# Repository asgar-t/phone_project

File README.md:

# 📱 Phone Project

A custom embedded hardware project built around an STM32 microcontroller and Quectel EC25 modem.  
The goal is to design, assemble, and program a complete phone system from the ground up — starting with hardware validation and moving toward a full integrated board.

---

## 🚀 Project Overview

**Step 1 — Hardware Verification (current step)** 
- Bring-up of the main board and peripheral circuits  
- Validate power rails, charging system, and USB interface  
- Test modem communication (EC25) and antenna performance  
- Ensure STM32 programming and serial communication are functional  

**Step 2 — Full System Integration**
- Run the STM32 firmware with modem control and battery management  
- Implement power sequencing and graceful shutdown logic  
- Test full end-to-end operation (voice/data + MCU control)  
- Optimize PCB layout and firmware reliability for production

---

## 🧠 Skills Demonstrated
- **PCB Design:** High-speed routing, impedance control, power delivery, and signal integrity  
- **Embedded Programming:** STM32 firmware (C), peripheral interfacing (UART, USB, GPIO, ADC)  
- **Power Systems:** Battery charging, voltage regulation, and load-sharing design  
- **System Integration:** Combining modem, MCU, and power management into a cohesive embedded system  

---

## ⚙️ Technologies & Components
- **MCU:** STM32 L4 Series
- **Modem:** Quectel EC25-AF  
- **Power:** USB-C input, Li-ion battery, charger IC 
- **Communication:** USB, UART, CAN 
- **Tools:** KiCad, STM32CubeIDE

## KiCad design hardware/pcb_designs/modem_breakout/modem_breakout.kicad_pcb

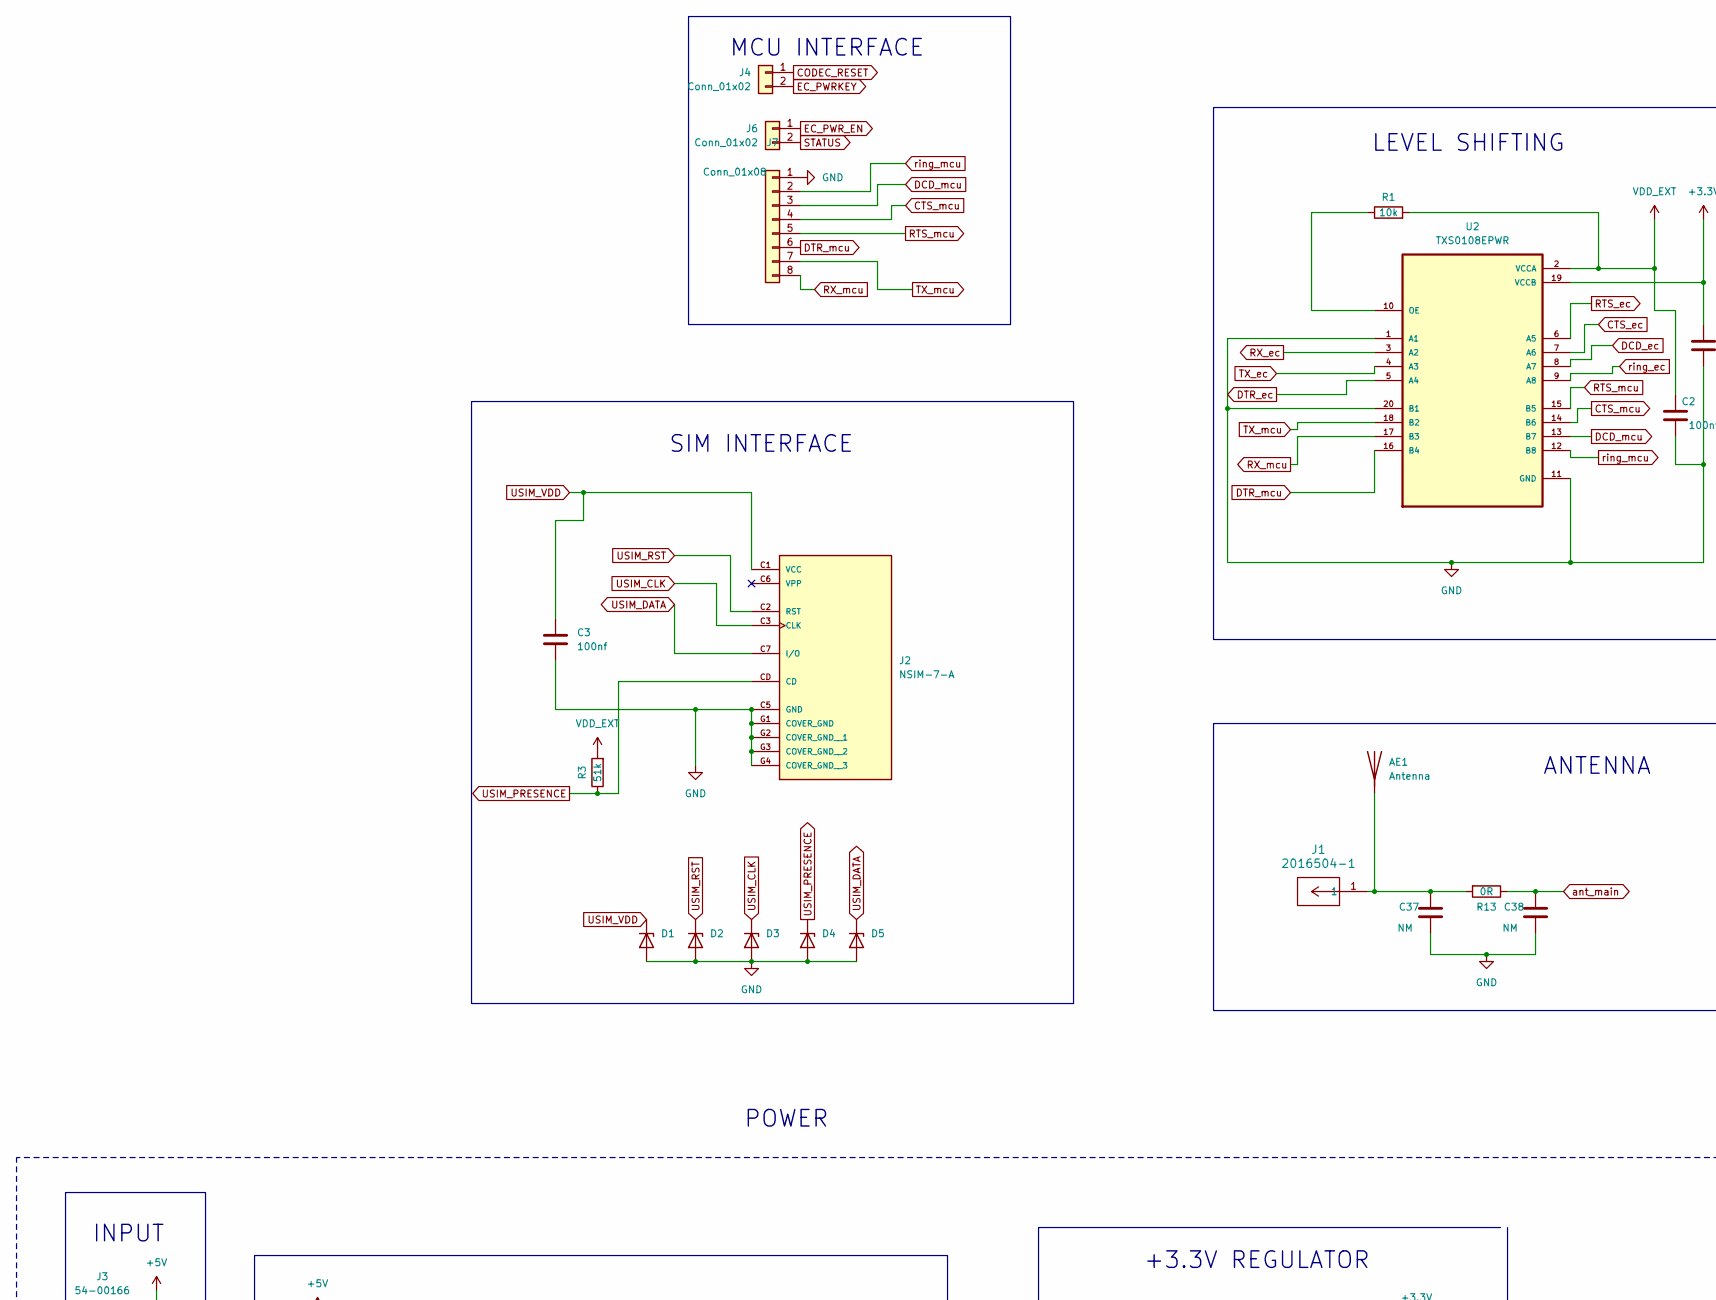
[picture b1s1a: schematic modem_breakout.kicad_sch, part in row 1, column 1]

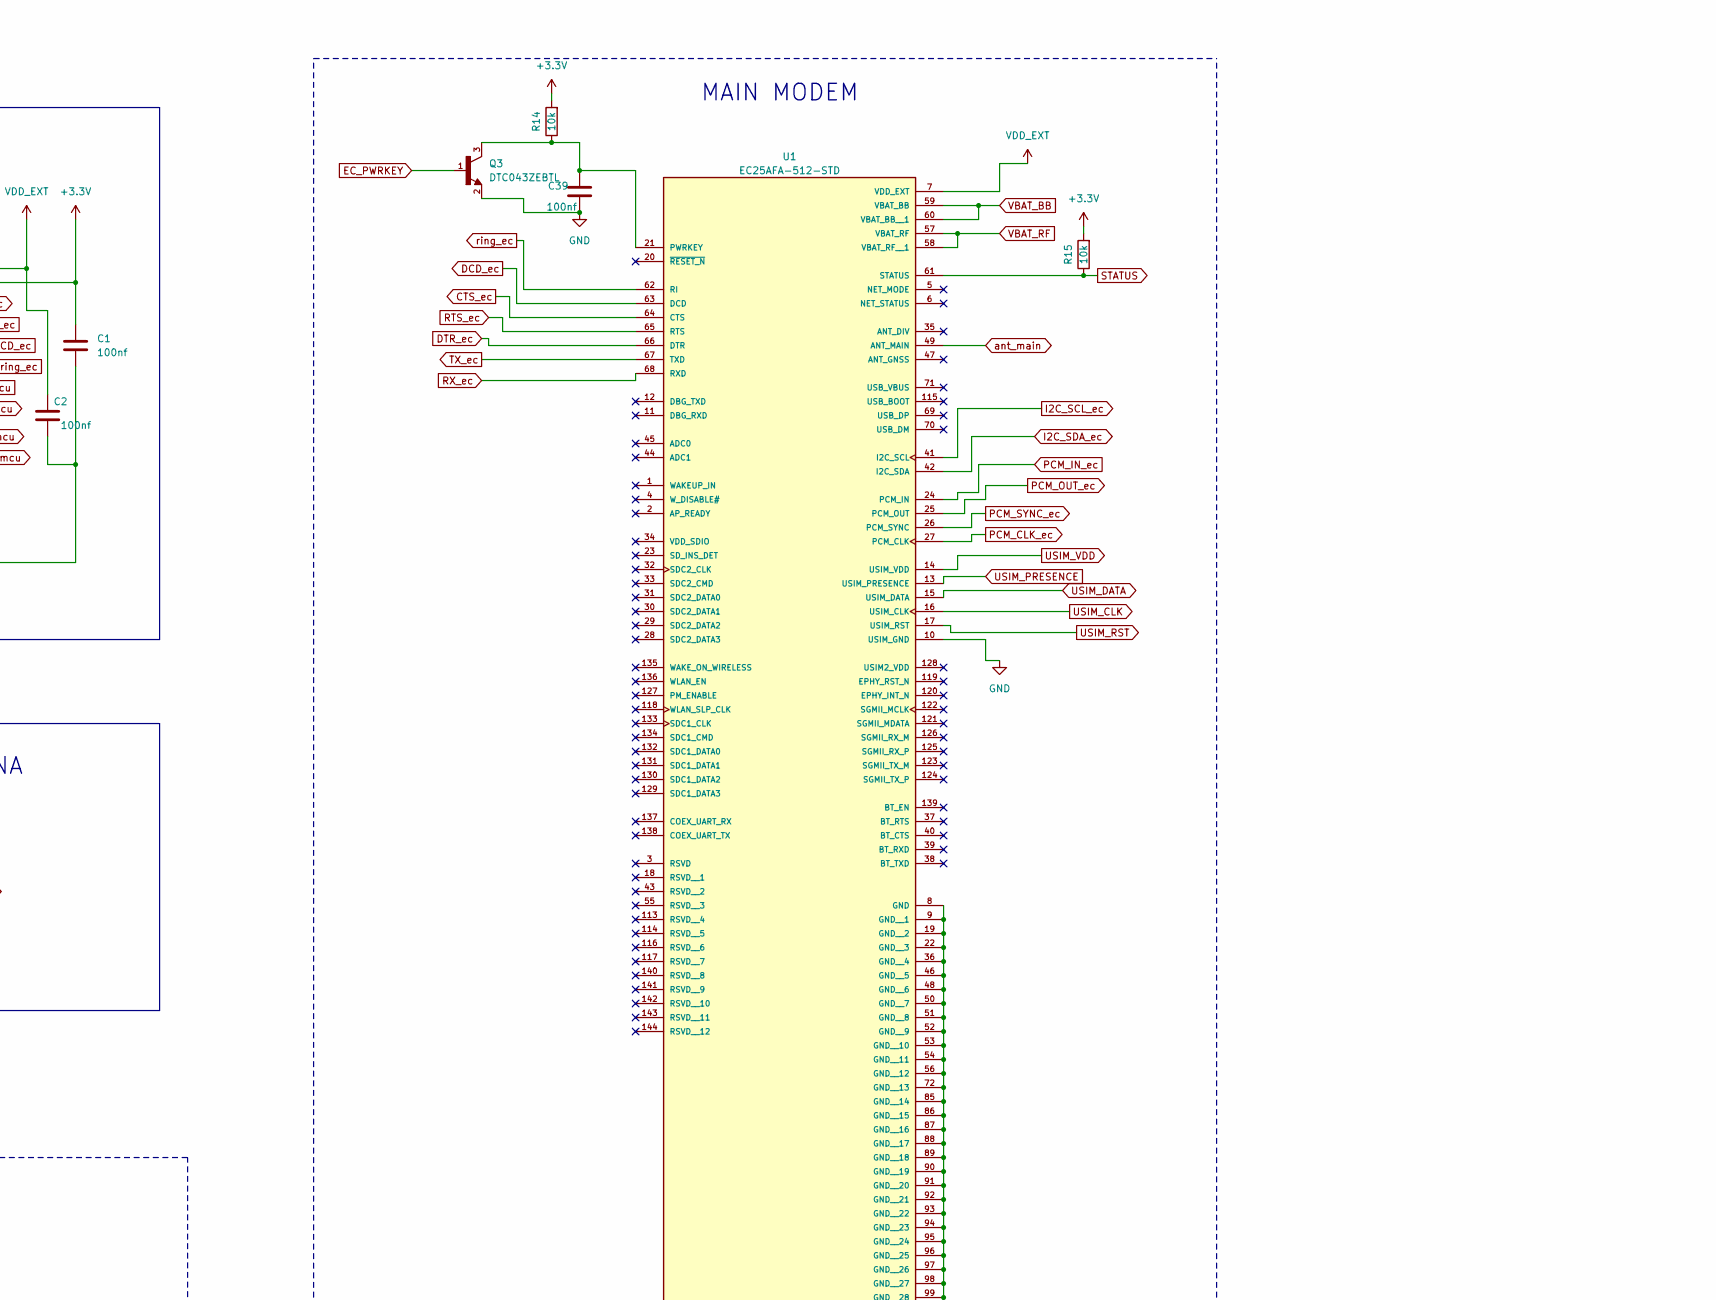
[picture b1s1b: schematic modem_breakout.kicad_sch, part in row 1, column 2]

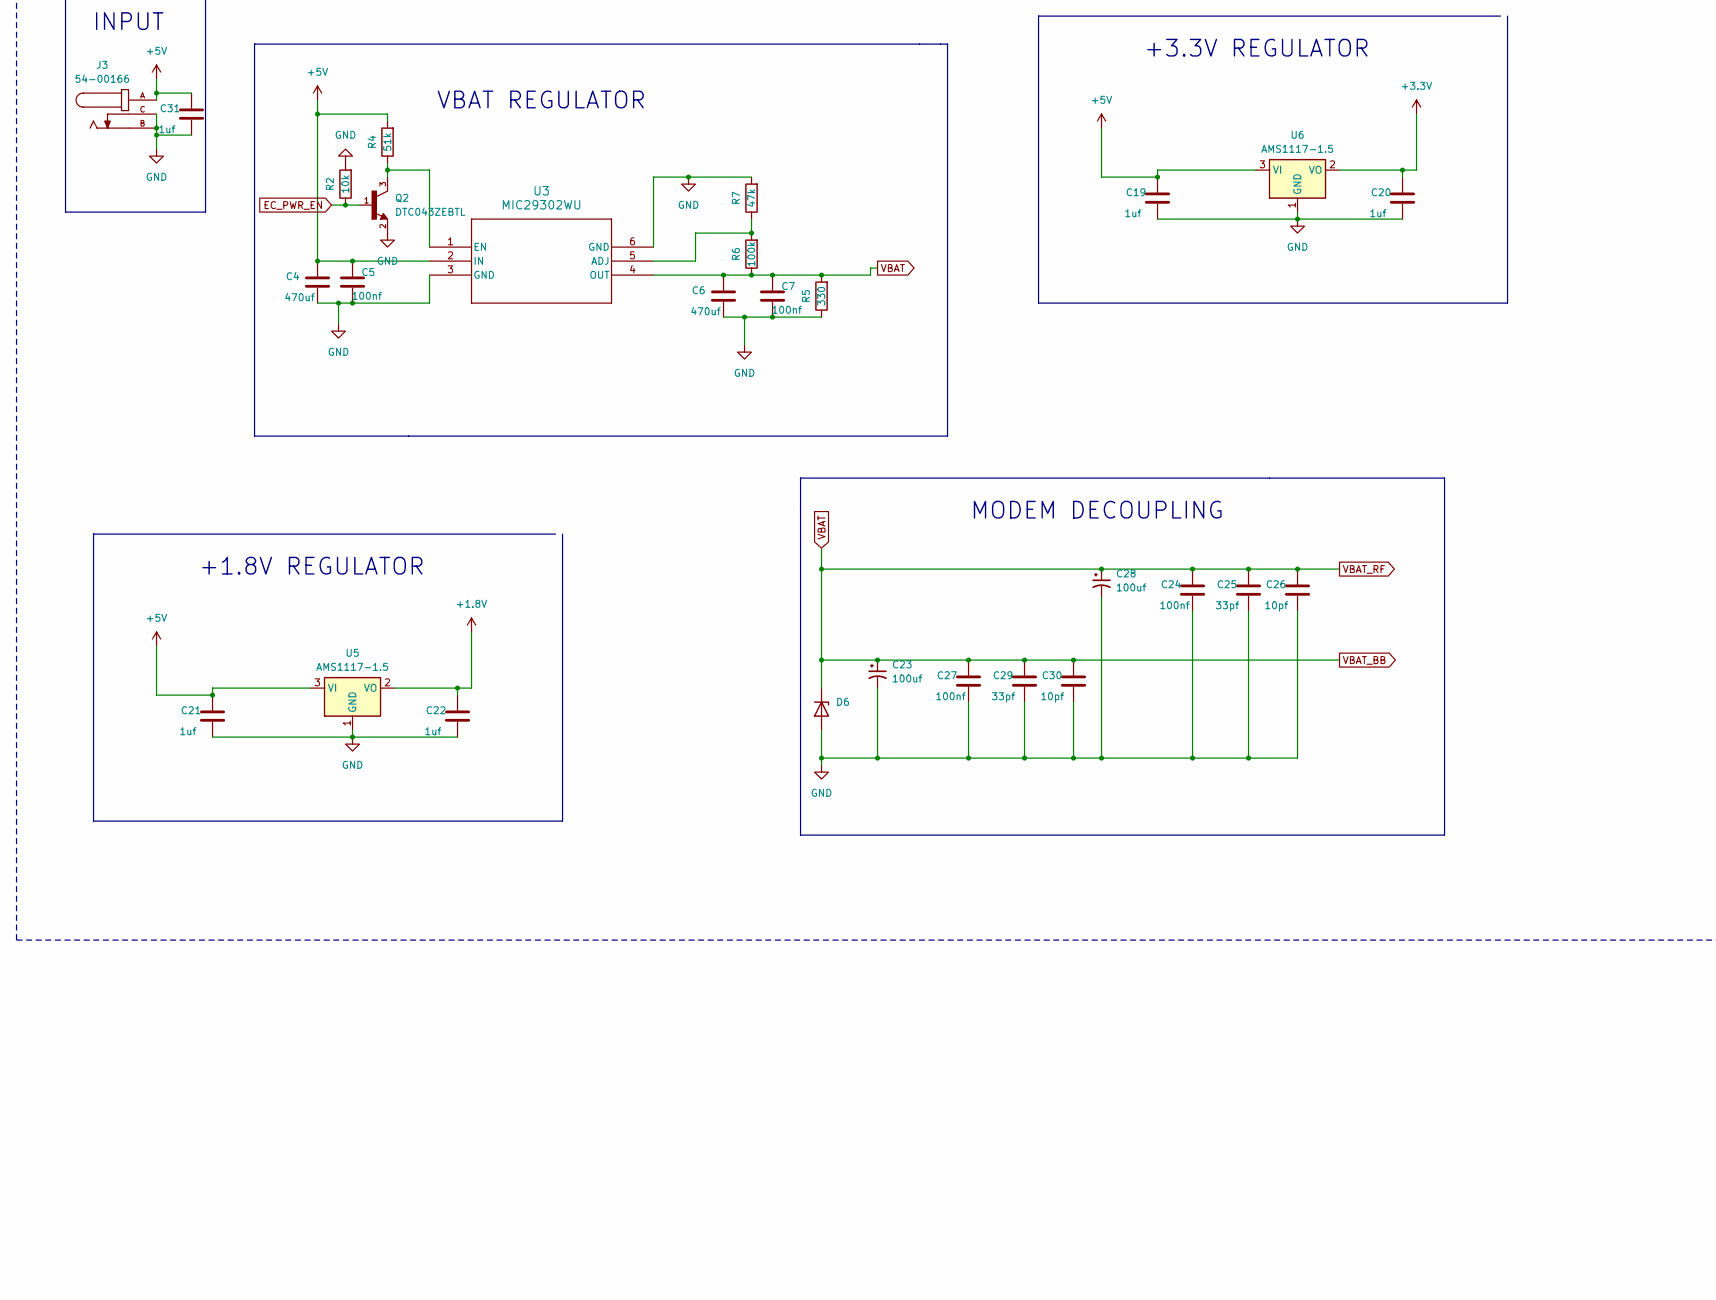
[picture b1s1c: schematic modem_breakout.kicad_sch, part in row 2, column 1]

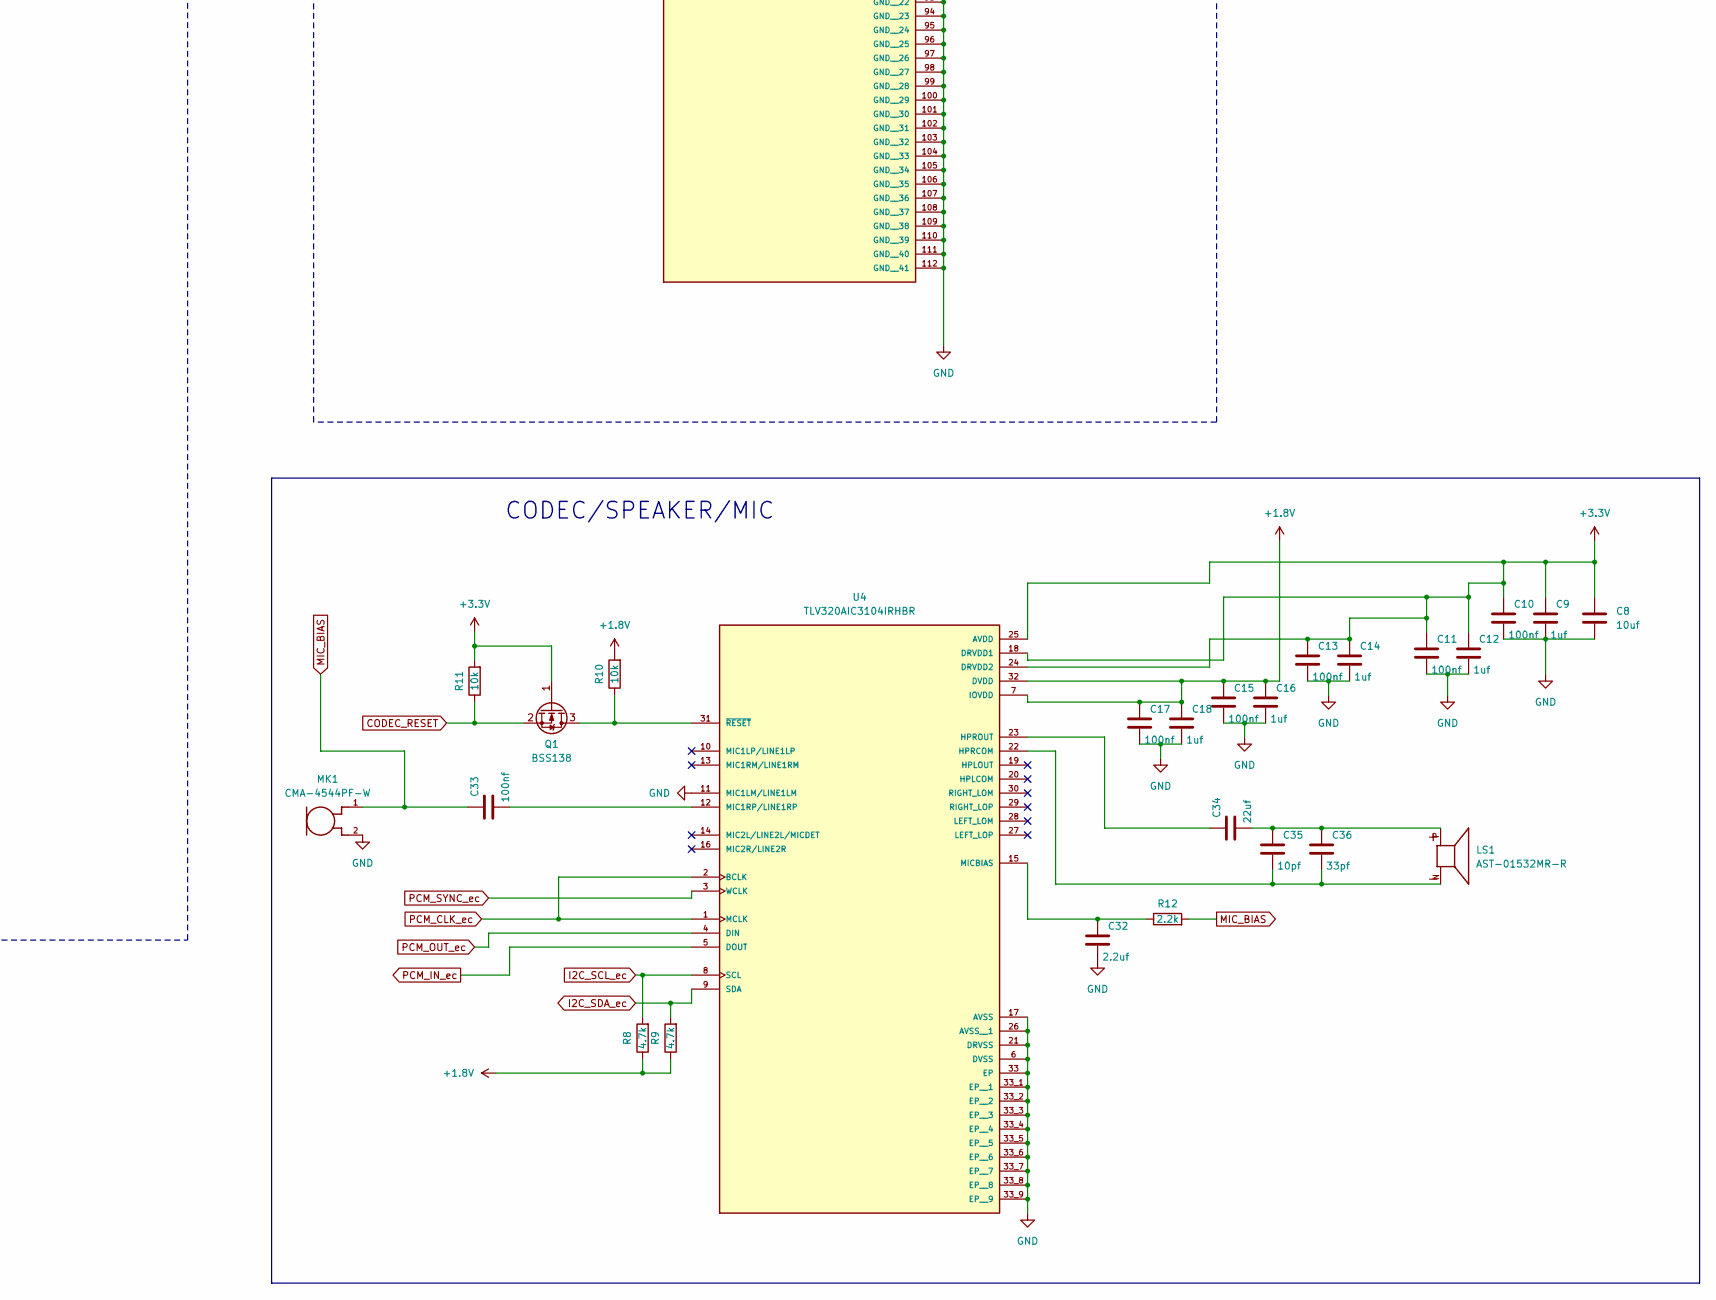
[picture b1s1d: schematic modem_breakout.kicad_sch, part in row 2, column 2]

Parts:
AE1: Antenna
C1, C2, C3, C5, C7, C24, C27, C33, C39: 100nf; C_0805_2012Metric_Pad1.18x1.45mm_HandSolder
C4, C6: 470uf; C_0805_2012Metric_Pad1.18x1.45mm_HandSolder
C8: 10uf; C_0402_1005Metric_Pad0.74x0.62mm_HandSolder
C9, C12, C14, C16, C18: 1uf; C_0402_1005Metric_Pad0.74x0.62mm_HandSolder
C10, C11, C13, C15, C17: 100nf; C_0402_1005Metric_Pad0.74x0.62mm_HandSolder
C19, C20, C21, C22, C31: 1uf; C_0805_2012Metric_Pad1.18x1.45mm_HandSolder
C23, C28: 100uf; C_0805_2012Metric_Pad1.18x1.45mm_HandSolder
C25, C29, C36: 33pf; C_0805_2012Metric_Pad1.18x1.45mm_HandSolder
C26, C30, C35: 10pf; C_0805_2012Metric_Pad1.18x1.45mm_HandSolder
C32: 2.2uf; C_0805_2012Metric_Pad1.18x1.45mm_HandSolder
C34: 22uf; C_0805_2012Metric_Pad1.18x1.45mm_HandSolder
C37, C38: NM; C_0805_2012Metric_Pad1.18x1.45mm_HandSolder
D1, D2, D3, D4, D5, D6: PTVS12VZ1USK; Nexperia_DSN1608-2_1.6x0.8mm
J1: 2016504-1; CONN1_2016504-1_TEC
J2: NSIM-7-A; new_sim; PARTREV 1.0
J3: 54-00166; barrel jack; PARTREV A
J4, J6: Conn_01x02; PinHeader_1x02_P2.54mm_Vertical
J7: Conn_01x08; PinHeader_1x08_P2.54mm_Vertical
LS1: AST-01532MR-R; SPKR_AST-01532MR-R; PARTREV A
MK1: CMA-4544PF-W; MIC_CMA-4544PF-W
Q1: BSS138; SOT-23
Q2, Q3: DTC043ZEBTL; SOTFL50P160X85-3N; PARTREV 002
R1, R2, R14, R15: 10k; C_0805_2012Metric_Pad1.18x1.45mm_HandSolder
R3, R4: 51k; C_0805_2012Metric_Pad1.18x1.45mm_HandSolder
R5: 330; C_0805_2012Metric_Pad1.18x1.45mm_HandSolder
R6: 100k; C_0805_2012Metric_Pad1.18x1.45mm_HandSolder
R7: 47k; C_0805_2012Metric_Pad1.18x1.45mm_HandSolder
R8, R9: 4.7k; C_0805_2012Metric_Pad1.18x1.45mm_HandSolder
R10, R11: 10k; C_0402_1005Metric_Pad0.74x0.62mm_HandSolder
R12: 2.2k; C_0805_2012Metric_Pad1.18x1.45mm_HandSolder
R13: 0R; C_0805_2012Metric_Pad1.18x1.45mm_HandSolder
U1: EC25AFA-512-STD; modem
U2: TXS0108EPWR; uart_translator
U3: MIC29302WU; vreg
U4: TLV320AIC3104IRHBR; new_codec
U5, U6: AMS1117-1.5; SOT-223-3_TabPin2

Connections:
+1.8V: C15.1, C16.1, C17.1, C18.1, C22.1, R8.1, R9.1, R10.2, U4.7 (IOVDD), U4.32 (DVDD), U5.2 (VO)
+3.3V: C1.1, C8.1, C9.1, C10.1, C11.1, C12.1, C13.1, C14.1, C20.1, Q1.1 (G), R11.2, R14.2, R15.2, U2.19 (VCCB), U4.18 (DRVDD1), U4.24 (DRVDD2), U4.25 (AVDD), U6.2 (VO)
+5V: C4.1, C5.1, C19.1, C21.1, C31.1, J3.A, R4.2, U3.2 (IN), U5.3 (VI), U6.3 (VI)
CODEC_RESET: J4.1, Q1.2 (S), R11.1
CTS_ec: U1.64 (CTS), U2.7 (A6)
CTS_mcu: J7.4, U2.14 (B6); also elsewhere on the board
DCD_ec: U1.63 (DCD), U2.8 (A7)
DCD_mcu: J7.3, U2.13 (B7); also elsewhere on the board
DTR_ec: U1.66 (DTR), U2.5 (A4)
DTR_mcu: J7.6, U2.16 (B4); also elsewhere on the board
EC_PWRKEY: J4.2, Q3.1
EC_PWR_EN: J6.1, Q2.1, R2.1
GND: C1.2, C2.2, C3.2, C4.2, C5.2, C6.2, C7.2, C8.2, C9.2, C10.2, C11.2, C12.2, C13.2, C14.2, C15.2, C16.2, C17.2, C18.2, C19.2, C20.2, C21.2, C22.2, C23.2, C24.2, C25.2, C26.2, C27.2, C28.2, C29.2, C30.2, C31.2, C32.2, C37.2, C38.2, C39.2, D1.2 (A), D2.2 (A), D3.2 (A), D4.2 (A), D5.2 (A), D6.2 (A), J2.C5 (GND), J2.G1 (COVER_GND), J2.G2 (COVER_GND__1), J2.G3 (COVER_GND__2), J2.G4 (COVER_GND__3), J3.B, J3.C, J7.1, MK1.2, Q2.2, Q3.2, R2.2, R5.1, R7.2, U1.8 (GND), U1.9 (GND__1), U1.10 (USIM_GND), U1.19 (GND__2), U1.22 (GND__3), U1.36 (GND__4), U1.46 (GND__5), U1.48 (GND__6), U1.50 (GND__7), U1.51 (GND__8), U1.52 (GND__9), U1.53 (GND__10), U1.54 (GND__11), U1.56 (GND__12), U1.72 (GND__13), U1.85 (GND__14), U1.86 (GND__15), U1.87 (GND__16), U1.88 (GND__17), U1.89 (GND__18), U1.90 (GND__19), U1.91 (GND__20), U1.92 (GND__21), U1.93 (GND__22), U1.94 (GND__23), U1.95 (GND__24), U1.96 (GND__25), U1.97 (GND__26), U1.98 (GND__27), U1.99 (GND__28), U1.100 (GND__29), U1.101 (GND__30), U1.102 (GND__31), U1.103 (GND__32), U1.104 (GND__33), U1.105 (GND__34), U1.106 (GND__35), U1.107 (GND__36), U1.108 (GND__37), U1.109 (GND__38), U1.110 (GND__39), U1.111 (GND__40), U1.112 (GND__41), U2.1 (A1), U2.11 (GND), U2.20 (B1), U3.3 (GND), U3.6 (GND), U4.6 (DVSS), U4.11 (MIC1LM/LINE1LM), U4.17 (AVSS), U4.21 (DRVSS), U4.26 (AVSS__1), U4.33 (EP), U4.33_1 (EP__1), U4.33_2 (EP__2), U4.33_3 (EP__3), U4.33_4 (EP__4), U4.33_5 (EP__5), U4.33_6 (EP__6), U4.33_7 (EP__7), U4.33_8 (EP__8), U4.33_9 (EP__9), U5.1 (GND), U6.1 (GND); also elsewhere on the board
I2C_SCL_ec: R8.2, U1.41 (I2C_SCL), U4.8 (SCL)
I2C_SDA_ec: R9.2, U1.42 (I2C_SDA), U4.9 (SDA)
MIC_BIAS: C33.1, MK1.1, R12.2
unnamed: AE1.1, C37.1, J1.1, R13.2
unnamed: C34.2, C35.1, C36.1, LS1.P
unnamed: Q1.3 (D), R10.1, U4.31 (~RESET)
unnamed: C39.1, Q3.3, R14.1, U1.21 (PWRKEY)
unnamed: R1.1, U2.10 (OE)
unnamed: R6.2, R7.1, U3.5 (ADJ)
unnamed: Q2.3, R4.1, U3.1 (EN)
unnamed: C35.2, C36.2, LS1.N, U4.22 (HPRCOM)
unnamed: C34.1, U4.23 (HPROUT)
unnamed: C33.2, U4.12 (MIC1RP/LINE1RP)
unnamed: C32.1, R12.1, U4.15 (MICBIAS)
PCM_CLK_ec: U1.27 (PCM_CLK), U4.1 (MCLK), U4.2 (BCLK)
PCM_IN_ec: U1.24 (PCM_IN), U4.5 (DOUT)
PCM_OUT_ec: U1.25 (PCM_OUT), U4.4 (DIN)
PCM_SYNC_ec: U1.26 (PCM_SYNC), U4.3 (WCLK)
RTS_ec: U1.65 (RTS), U2.6 (A5)
RTS_mcu: J7.5, U2.15 (B5); also elsewhere on the board
RX_ec: U1.68 (RXD), U2.3 (A2)
RX_mcu: J7.8, U2.17 (B3); also elsewhere on the board
STATUS: J6.2, R15.1, U1.61 (STATUS)
TX_ec: U1.67 (TXD), U2.4 (A3)
TX_mcu: J7.7, U2.18 (B2); also elsewhere on the board
USIM_CLK: D3.1 (K), J2.C3 (CLK), U1.16 (USIM_CLK)
USIM_DATA: D5.1 (K), J2.C7 (I/O), U1.15 (USIM_DATA)
USIM_PRESENCE: D4.1 (K), J2.CD, R3.1, U1.13 (USIM_PRESENCE)
USIM_RST: D2.1 (K), J2.C2 (RST), U1.17 (USIM_RST)
USIM_VDD: C3.1, D1.1 (K), J2.C1 (VCC), U1.14 (USIM_VDD)
VBAT: C6.1, C7.1, C23.1, C24.1, C25.1, C26.1, C27.1, C28.1, C29.1, C30.1, D6.1 (K), R5.2, R6.1, U1.57 (VBAT_RF), U1.58 (VBAT_RF__1), U1.59 (VBAT_BB), U1.60 (VBAT_BB__1), U3.4 (OUT)
VDD_EXT: C2.1, R1.2, R3.2, U1.7 (VDD_EXT), U2.2 (VCCA)
ant_main: C38.1, R13.1, U1.49 (ANT_MAIN)
ring_ec: U1.62 (RI), U2.9 (A8)
ring_mcu: J7.2, U2.12 (B8); also elsewhere on the board

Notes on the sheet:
MCU INTERFACE
CODEC/SPEAKER/MIC
MODEM DECOUPLING
LEVEL SHIFTING
SIM INTERFACE
MAIN MODEM
ANTENNA
+3.3V REGULATOR
+1.8V REGULATOR
VBAT REGULATOR
POWER
INPUT

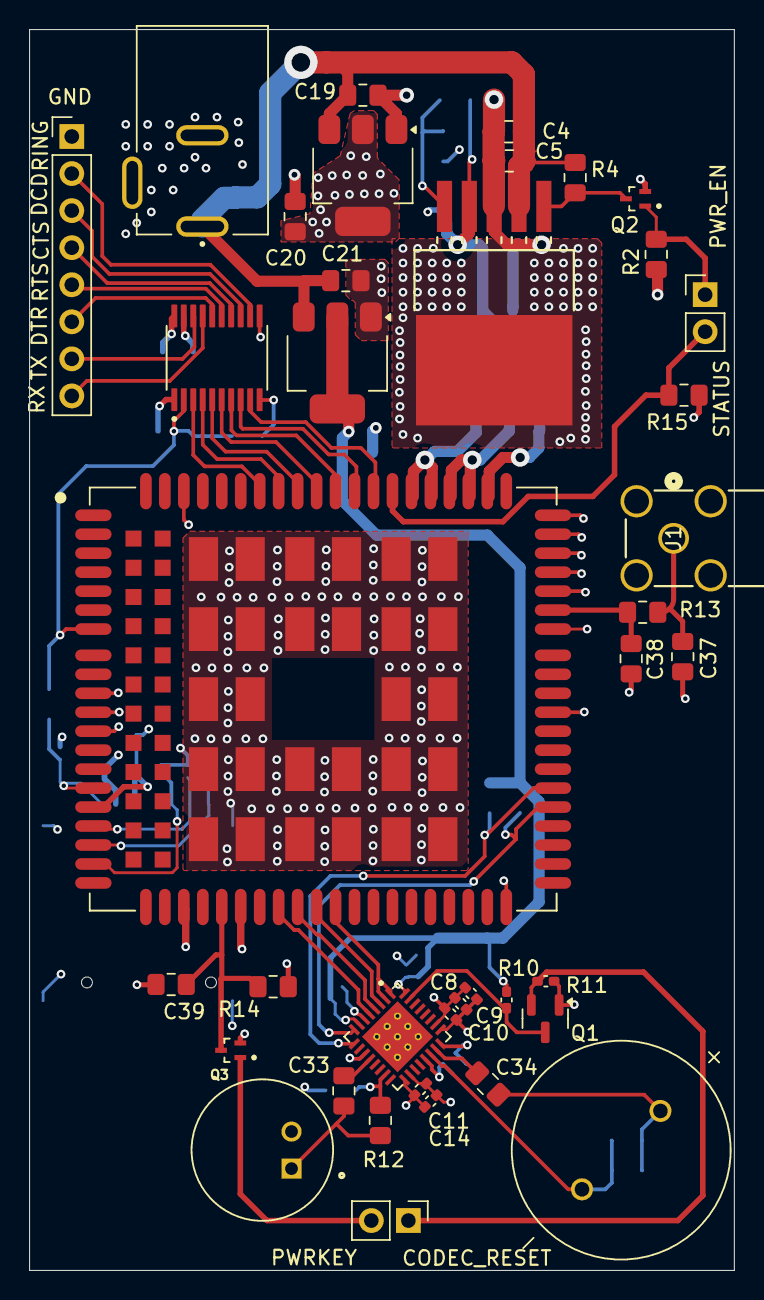
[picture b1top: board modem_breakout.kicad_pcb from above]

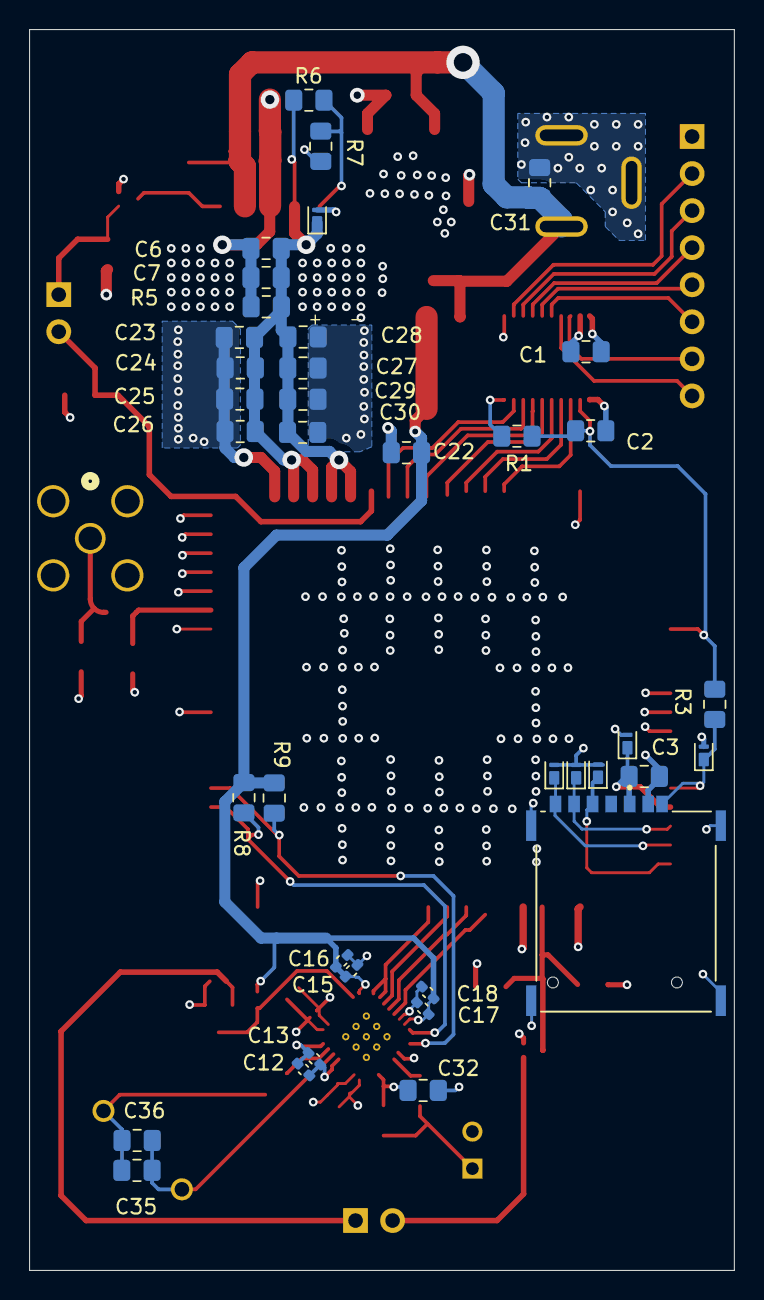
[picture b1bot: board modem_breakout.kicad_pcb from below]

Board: 4 copper layers, 48.3 x 85.1 mm, 77 parts (38 on the bottom side), 48 nets.

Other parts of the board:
GND: Conn_01x08; PinHeader_1x08_P2.54mm_Vertical

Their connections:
CTS_mcu: GND.4; also elsewhere on the board
DCD_mcu: GND.3; also elsewhere on the board
DTR_mcu: GND.6; also elsewhere on the board
GND: GND.1; also elsewhere on the board
RTS_mcu: GND.5; also elsewhere on the board
RX_mcu: GND.8; also elsewhere on the board
TX_mcu: GND.7; also elsewhere on the board
ring_mcu: GND.2; also elsewhere on the board

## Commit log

2025-11-01 rework tree
2025-11-06 finalize testbench design
2025-11-07 final - ordered
2025-11-07 reorganizing
2025-11-07 software
2025-11-07 started setting up for modem testing
2025-11-07 uart/putty working
2025-12-11 modem/putty interface
2025-12-20 uart interface set up
